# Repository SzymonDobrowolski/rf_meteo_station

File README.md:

# 🌤️ RF Meteo Station - Custom ESP32 Weather System

A complete, end-to-end open-source weather station project. This system combines custom hardware design, 3D-printed enclosures, and an advanced multithreaded firmware architecture to deliver a modern, touch-enabled weather dashboard.

---

## 1. ⚡ PCB Design (Custom Hardware)
The hardware architecture is divided into two separate custom-designed printed circuit boards:

* **Main Indoor Unit:** Houses the ESP32 microcontroller, power management, display connector (SPI), and the nRF24L01 radio receiver.
* **External Sensor Node:** A low-power, battery-operated board featuring environmental sensors and an nRF24L01 transmitter to send data wirelessly to the main unit.

| Main Board | External Sensor Board |
|:---:|:---:|
|  |  |

**📄 Full Schematics (PDF):**
* [Open Main Board Schematic PDF](images/int_scheme.pdf)
* [Open Sensor Board Schematic PDF](images/ext_scheme.pdf)

---

## 2. 🧊 Enclosure Design (3D Models)
To make the project a fully finished product, custom enclosures were modeled from scratch and 3D printed.

* **Main Display Case:** Designed to perfectly fit the touch screen, custom PCB, and provide easy access to power ports.
* **Outdoor Sensor Shield:** Features a Stevenson screen-inspired design to protect the external PCB from rain and direct sunlight while allowing accurate temperature and humidity readings.

| Display Enclosure | Sensor Enclosure |
|:---:|:---:|
|  |  |

---

## 3. 💻 Code Architecture & Features
The firmware is built on top of the **ESP-IDF** framework and utilizes **FreeRTOS** to handle multiple background tasks without blocking the UI. 

### Key Software Features:
* **Advanced GUI (LVGL):** A fluid, touch-optimized interface featuring a dashboard, 24h interactive charts, and a 7-day forecast. The UI logic is completely decoupled from the system core.
* **Multithreading:** Dedicated FreeRTOS tasks for display rendering, wireless data receiving (nRF24L01), and Wi-Fi management.
* **Live Weather API:** Fetches and parses real-time forecast data via the Open-Meteo API using `cJSON`.
* **Smart Power Management:** Features a Day/Night mode with a PWM soft-start mechanism to prevent sudden power spikes and brownout resets.
* **NVS Storage:** Safely retains Wi-Fi credentials, location preferences, and brightness settings between reboots.
* **SNTP Time Sync:** Automatically maintains atom-accurate system time in the background.
* **Display Support:** Codebase is optimized for **ST7789** controllers with easy migration to **ILI9341** via the `esp_lcd` framework.

---

## 4. 🚀 How to Build & Flash
The software is designed for the Espressif ESP-IDF framework (v5.0 or newer).

**Step 1: Clone the repository**
```bash
git clone [https://github.com/SzymonDobrowolski/rf_meteo_station.git](https://github.com/SzymonDobrowolski/rf_meteo_station.git)
cd rf_meteo_station/ESP32_int_station_code/internal_module_code_ST7789
```

**Step 2: Install Display Dependencies (ILI9341 Only)**
*Note: The default codebase is optimized for the ST7789 controller. If your specific build uses the ILI9341 display, you must add the official driver component before building:*
```bash
idf.py add-dependency "espressif/esp_lcd_ili9341"
```

**Step 3: Build and Flash**
Connect your ESP32 board and run the following commands:
```bash
idf.py set-target esp32
idf.py build
idf.py -p (YOUR_PORT) flash monitor
```

---

## 5. 🌟 Final Result
Here is the fully assembled, programmed, and working RF Meteo Station in action!

<p align="center">
  
  &nbsp;
  
</p>

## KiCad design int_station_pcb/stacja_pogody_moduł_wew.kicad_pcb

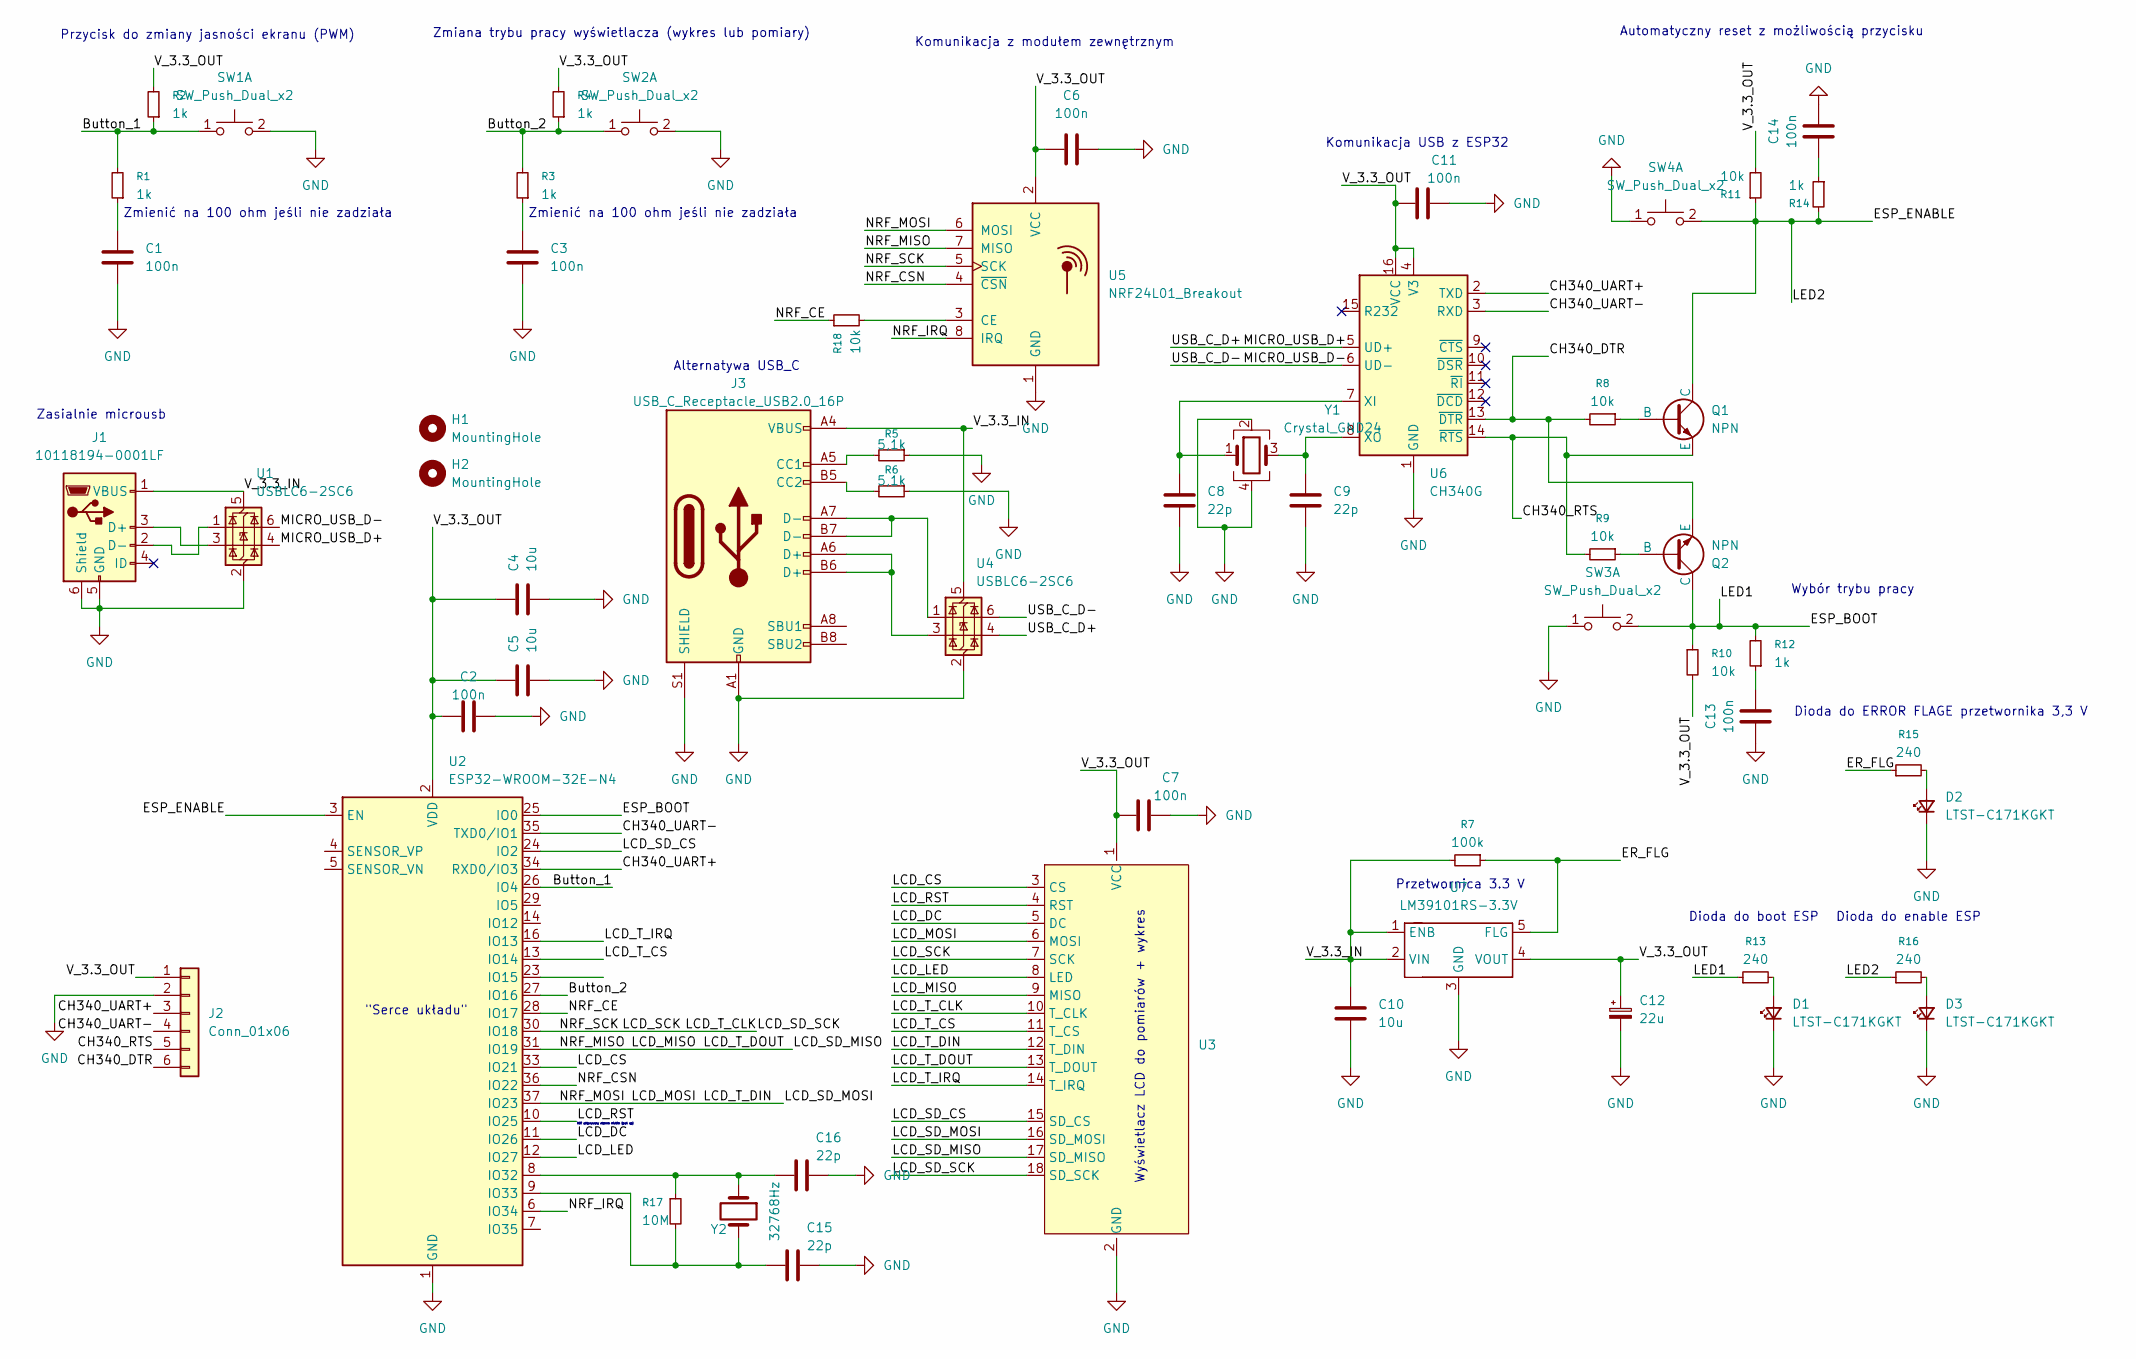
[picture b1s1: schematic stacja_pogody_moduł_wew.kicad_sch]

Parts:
C1, C2, C3, C6, C7, C11, C13, C14: 100n; C_0603_1608Metric_Pad1.08x0.95mm_HandSolder
C4, C5, C10: 10u; C_0805_2012Metric_Pad1.18x1.45mm_HandSolder
C8, C9: 22p; C_0805_2012Metric_Pad1.18x1.45mm_HandSolder
C12: 22u; CP_EIA-3528-21_Kemet-B_HandSolder
C15, C16: 22p; C_0603_1608Metric_Pad1.08x0.95mm_HandSolder
D1, D2, D3: LTST-C171KGKT; LED_0805_2012Metric
H1, H2: MountingHole; MountingHole_3.2mm_M3
J1: 10118194-0001LF; USB_Micro-B_Amphenol_10118194-0001LF_Horizontal
J2: Conn_01x06; PinSocket_1x06_P2.54mm_Vertical
J3: USB_C_Receptacle_USB2.0_16P; USB_C_Receptacle_TME
Q1, Q2: NPN; SOT-23_Handsoldering
R1, R2, R3, R4, R12, R14: 1k; R_0603_1608Metric
R5, R6: 5,1k; R_0603_1608Metric
R7: 100k; R_0603_1608Metric
R8, R9, R10, R11, R18: 10k; R_0603_1608Metric
R13, R15, R16: 240; R_0603_1608Metric
R17: 10M; R_0603_1608Metric
SW1, SW2, SW3, SW4: SW_Push_Dual_x2; SW_PUSH_6mm_H4.3mm
U1, U4: USBLC6-2SC6; SOT-23-6
U2: ESP32-WROOM-32E-N4; ESP32-WROOM-32E
U3: LCD_2_8
U5: NRF24L01_Breakout; nRF24L01_Breakout
U6: CH340G; SOIC-16_3.9x9.9mm_P1.27mm
U7: LM39101RS-3.3V; TO-252-5_TabPin3
Y1: Crystal_GND24; Crystal_SMD_3225-4Pin_3.2x2.5mm_HandSoldering
Y2: 32768Hz; Crystal_DS26_D2.0mm_L6.0mm_Horizontal

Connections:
/Button_1: R1.2, R2.1, SW1.1 (C), U2.26 (IO4)
/Button_2: R3.2, R4.1, SW2.1 (C), U2.27 (IO16)
/CH340_DTR: J2.6, Q2.3 (E), R8.2, U6.13 (~DTR)
/CH340_RTS: J2.5, Q1.3 (E), R9.2, U6.14 (~RTS)
/CH340_UART+: J2.3, U2.34 (RXD0/IO3), U6.2 (TXD)
/CH340_UART-: J2.4, U2.35 (TXD0/IO1), U6.3 (RXD)
/ER_FLG: R7.1, R15.1, U7.5 (FLG)
/ESP_BOOT: Q2.1 (C), R10.1, R12.2, R13.1, SW3.2 (D), U2.25 (IO0)
/ESP_ENABLE: Q1.1 (C), R11.1, R14.2, R16.1, SW4.2 (D), U2.3 (EN)
/LCD_CS: U2.33 (IO21), U3.3 (CS)
/LCD_DC: U2.11 (IO26), U3.5 (DC)
/LCD_LED: U2.12 (IO27), U3.8 (LED)
/LCD_MISO: U2.31 (IO19), U3.9 (MISO), U3.13 (T_DOUT), U3.17 (SD_MISO), U5.7 (MISO)
/LCD_MOSI: U2.37 (IO23), U3.6 (MOSI), U3.12 (T_DIN), U3.16 (SD_MOSI), U5.6 (MOSI)
/LCD_RST: U2.10 (IO25), U3.4 (RST)
/LCD_SCK: U2.30 (IO18), U3.7 (SCK), U3.10 (T_CLK), U3.18 (SD_SCK), U5.5 (SCK)
/LCD_SD_CS: U2.24 (IO2), U3.15 (SD_CS)
/LCD_T_CS: U2.13 (IO14), U3.11 (T_CS)
/LCD_T_IRQ: U2.16 (IO13), U3.14 (T_IRQ)
/MICRO_USB_D+: U1.4 (I/O2), U4.4 (I/O2), U6.5 (UD+)
/MICRO_USB_D-: U1.6 (I/O1), U4.6 (I/O1), U6.6 (UD-)
/NRF_CE: R18.1, U2.28 (IO17)
/NRF_CSN: U2.36 (IO22), U5.4 (~CSN)
/NRF_IRQ: U2.6 (IO34), U5.8 (IRQ)
/V_3.3_IN: C10.2, J1.1 (VBUS), J3.A4 (VBUS), J3.A9 (VBUS), J3.B4 (VBUS), J3.B9 (VBUS), R7.2, U1.5 (VBUS), U4.5 (VBUS), U7.1 (ENB), U7.2 (VIN)
/V_3.3_OUT: C2.2, C4.2, C5.2, C6.2, C7.2, C11.2, C12.1, J2.1, R2.2, R4.2, R10.2, R11.2, U2.2 (VDD), U3.1 (VCC), U5.2 (VCC), U6.4 (V3), U6.16 (VCC), U7.4 (VOUT)
GND: C1.1, C2.1, C3.1, C4.1, C5.1, C6.1, C7.1, C8.2, C9.2, C10.1, C11.1, C12.2, C13.2, C14.2, C15.1, C16.1, D1.1 (K), D2.1 (K), D3.1 (K), J1.5 (GND), J1.6 (Shield), J2.2, J3.A1 (GND), J3.A12 (GND), J3.B1 (GND), J3.B12 (GND), J3.S1 (SHIELD), R5.1, R6.1, SW1.2 (D), SW2.2 (D), SW3.1 (C), SW4.1 (C), U1.2 (GND), U2.1 (GND), U2.15 (GND), U2.38 (GND), U2.39 (GND), U3.2 (GND), U4.2 (GND), U5.1 (GND), U6.1 (GND), U7.3 (GND), Y1.2, Y1.4
unnamed: C1.2, R1.1
unnamed: C3.2, R3.1
unnamed: C13.1, R12.1
unnamed: C14.1, R14.1
unnamed: D1.2 (A), R13.2
unnamed: D2.2 (A), R15.2
unnamed: D3.2 (A), R16.2
unnamed: J1.3 (D+), U1.3 (I/O2)
unnamed: J1.2 (D-), U1.1 (I/O1)
unnamed: J3.A5 (CC1), R5.2
unnamed: J3.B5 (CC2), R6.2
unnamed: J3.A6 (D+), J3.B6 (D+), U4.3 (I/O2)
unnamed: J3.A7 (D-), J3.B7 (D-), U4.1 (I/O1)
unnamed: Q1.2 (B), R8.1
unnamed: Q2.2 (B), R9.1
unnamed: C16.2, R17.1, U2.8 (IO32), Y2.1
unnamed: C15.2, R17.2, U2.9 (IO33), Y2.2
unnamed: R18.2, U5.3 (CE)
unnamed: C8.1, U6.7 (XI), Y1.1
unnamed: C9.1, U6.8 (XO), Y1.3

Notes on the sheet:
Wyświetlacz LCD do pomiarów + wykres
Komunikacja z modułem zewnętrznym
Zmienić na 100 ohm jeśli nie zadziała
Zasialnie microusb
Wybór trybu pracy
Dioda do enable ESP
Automatyczny reset z możliwością przycisku
Dioda do boot ESP
RST aktywowany stanem niskim (pull up)
Alternatywa USB_C
Dioda do ERROR FLAGE przetwornika 3,3 V
Komunikacja USB z ESP32
Zmiana trybu pracy wyświetlacza (wykres lub pomiary)
Przycisk do zmiany jasności ekranu (PWM)
"Serce układu"
Przetwornica 3.3 V

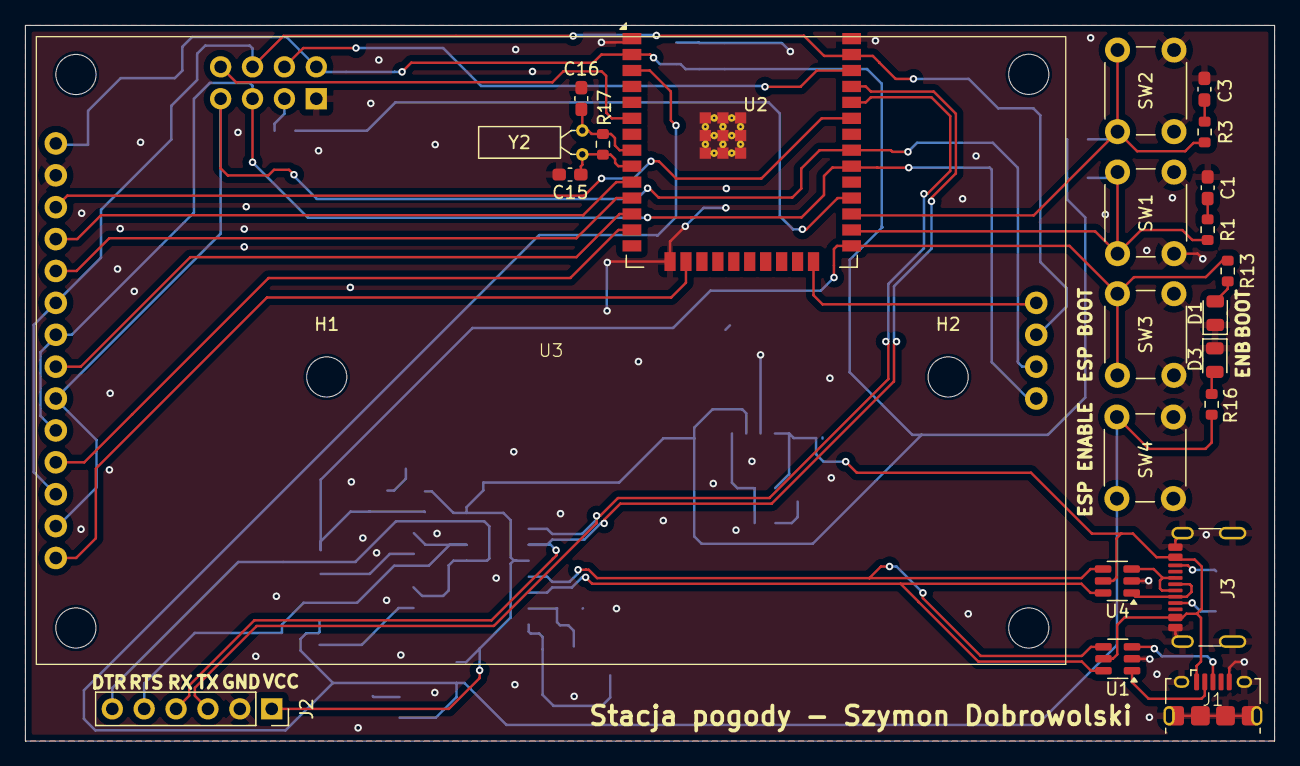
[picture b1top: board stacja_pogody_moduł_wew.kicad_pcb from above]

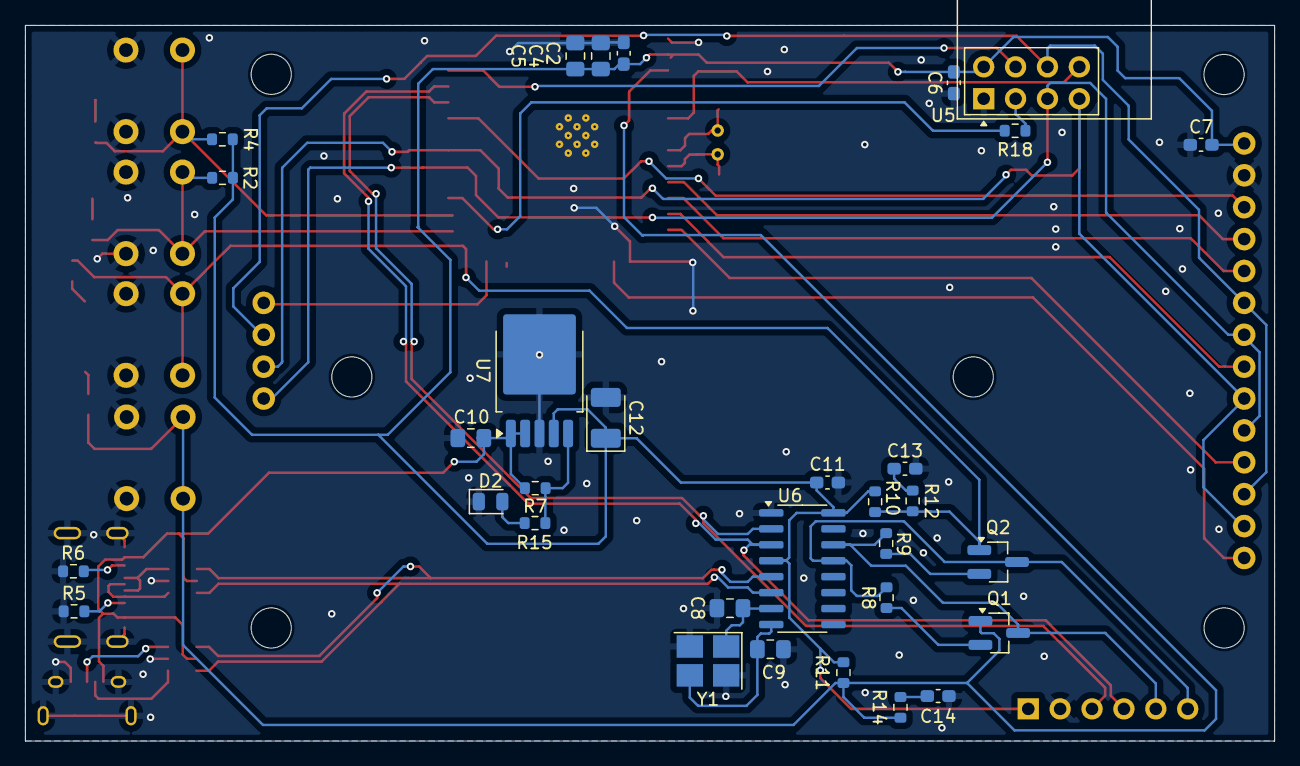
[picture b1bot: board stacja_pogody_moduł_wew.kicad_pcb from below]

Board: 2 copper layers, 99.5 x 57.0 mm, 57 parts (32 on the bottom side), 47 nets.

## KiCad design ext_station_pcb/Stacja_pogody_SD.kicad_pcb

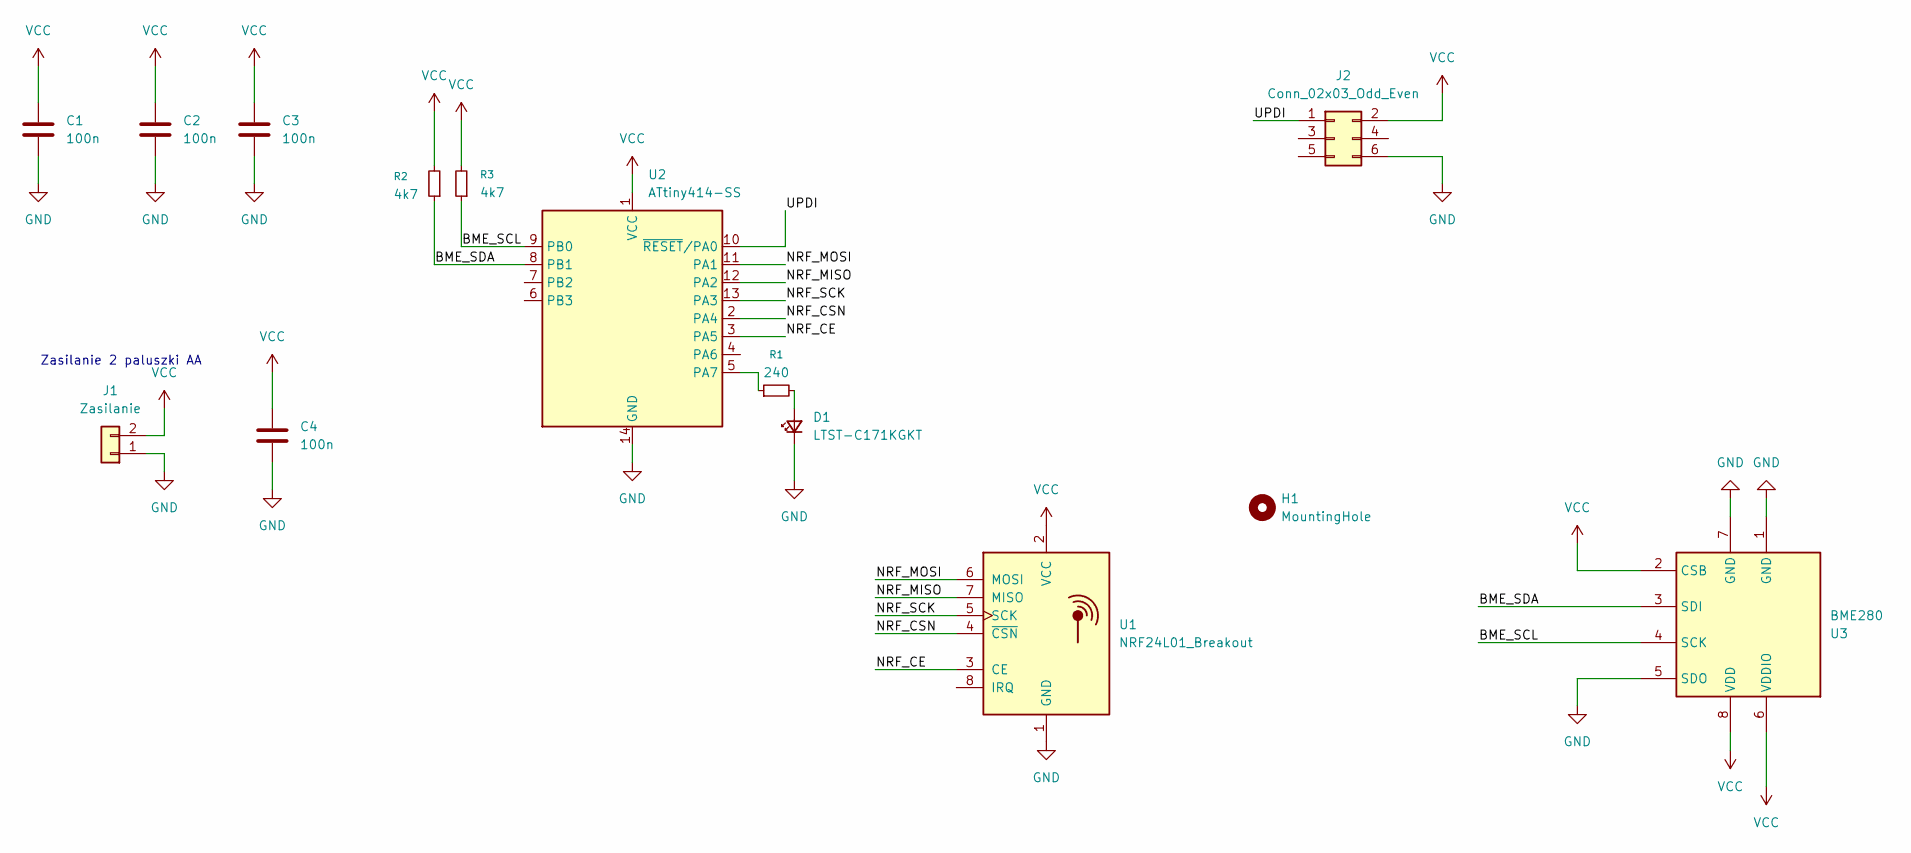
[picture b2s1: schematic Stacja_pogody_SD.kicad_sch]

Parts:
C1, C2, C3, C4: 100n; C_0603_1608Metric
D1: LTST-C171KGKT; LED_0805_2012Metric
H1: MountingHole; MountingHole_3.2mm_M3
J1: Zasilanie; PinHeader_1x02_P2.54mm_Vertical
J2: Conn_02x03_Odd_Even; PinHeader_2x03_P2.54mm_Vertical
R1: 240; R_0603_1608Metric
R2, R3: 4k7; R_0603_1608Metric
U1: NRF24L01_Breakout; nRF24L01_Breakout
U2: ATtiny414-SS; SOIC-14_3.9x8.7mm_P1.27mm
U3: BME280; Bosch_LGA-8_2.5x2.5mm_P0.65mm_ClockwisePinNumbering

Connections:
/BME_SCL: R3.1, U2.9 (PB0), U3.4 (SCK)
/BME_SDA: R2.1, U2.8 (PB1), U3.3 (SDI)
/NRF_CE: U1.3 (CE), U2.3 (PA5)
/NRF_CSN: U1.4 (~CSN), U2.2 (PA4)
/NRF_MISO: U1.7 (MISO), U2.12 (PA2)
/NRF_MOSI: U1.6 (MOSI), U2.11 (PA1)
/NRF_SCK: U1.5 (SCK), U2.13 (PA3)
/UPDI: J2.1, U2.10 (~RESET/PA0)
GND: C1.1, C2.1, C3.1, C4.1, D1.1 (K), J1.1, J2.6, U1.1 (GND), U2.14 (GND), U3.1 (GND), U3.5 (SDO), U3.7 (GND)
unnamed: D1.2 (A), R1.2
unnamed: R1.1, U2.5 (PA7)
VCC: C1.2, C2.2, C3.2, C4.2, J1.2, J2.2, R2.2, R3.2, U1.2 (VCC), U2.1 (VCC), U3.2 (CSB), U3.6 (VDDIO), U3.8 (VDD)

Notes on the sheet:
Zasilanie 2 paluszki AA

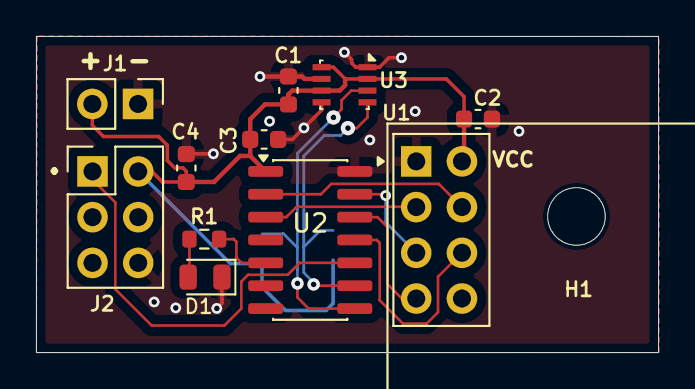
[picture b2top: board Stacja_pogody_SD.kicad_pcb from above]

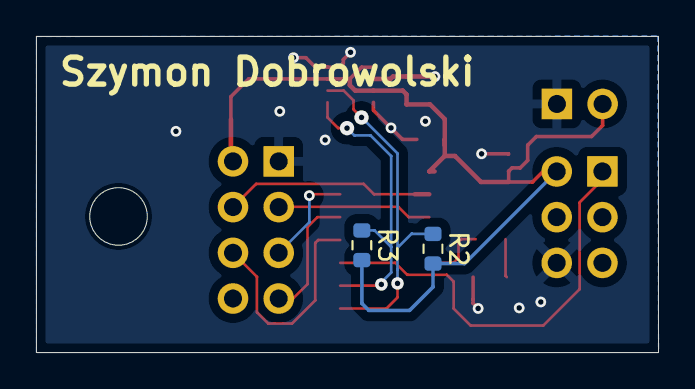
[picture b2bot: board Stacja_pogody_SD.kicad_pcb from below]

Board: 2 copper layers, 34.6 x 17.6 mm, 14 parts (2 on the bottom side), 12 nets.

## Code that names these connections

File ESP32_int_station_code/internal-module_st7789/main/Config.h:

#pragma once
#define BUTTON_1 GPIO_NUM_36
#define BUTTON_2 GPIO_NUM_39

#define LED1 GPIO_NUM_13
#define LED2 GPIO_NUM_21

// SPI Pins
#define SPI_MISO GPIO_NUM_19
#define SPI_MOSI GPIO_NUM_23
#define SPI_SCLK GPIO_NUM_18

// NRF Pins
#define NRF_CE_PIN GPIO_NUM_22
#define NRF_CSN_PIN GPIO_NUM_16
//NRF Settings
#define RX_ADDRESS_VAL {'A', 'T', '4', '1', '4'}
#define Channel 76
#define NRF_SPEED 0x07 //2Mbps, 0dBm

// --- STRUKTURA DANYCH (12 bajtów) ---
typedef struct __attribute__((packed)) {
    int32_t temp_hundredths;
    uint32_t pressure_pa;
    uint32_t hum_x1024;
} SensorData;

// LCD Pins
#define CS_PIN GPIO_NUM_4
#define DC_PIN GPIO_NUM_26
#define RESET_PIN GPIO_NUM_25
#define BL_PIN GPIO_NUM_27
//LCD Settings
#define LCD_TYPE 0x7789
#define LCD_WIDTH  320
#define LCD_HEIGHT 240
//Optional LCD
#define T_CS GPIO_NUM_14
#define SD_CS GPIO_NUM_17

#define NRF_IRQ GPIO_NUM_34
#define T_IRQ GPIO_NUM_35

// NTC
#define SSID "POCO X3 NFC"
#define PASSWORD "Rafik123"
#define SNTP_SERVER "pool.ntp.org"

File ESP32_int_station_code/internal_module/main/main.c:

#include <stdio.h>
#include <string.h>
#include <driver/gpio.h>
#include <driver/spi_master.h>
#include <freertos/FreeRTOS.h>
#include <freertos/task.h>
#include <esp_spiffs.h>
#include <esp_log.h>

#include "ili9340.h"
#include "fontx.h"

#include "NRF24L01.h"


#define PIN_LCD_CS     4
#define PIN_LCD_DC     26
#define PIN_LCD_RST    25
#define PIN_LCD_LED    27

#define PIN_MISO 19
#define PIN_MOSI 23
#define PIN_SCK  18

typedef struct __attribute__((packed)) {
    float temperature_C;
    float humidity_pct;
    float pressure_hPa;
} sensor_packet_t;

spi_device_handle_t nrf_spi;
spi_device_handle_t spi_lcd;

void spi_bus_init()
{
    spi_bus_config_t buscfg = {
        .mosi_io_num = PIN_MOSI,
        .miso_io_num = PIN_MISO,
        .sclk_io_num = PIN_SCK,
        .quadwp_io_num = -1,
        .quadhd_io_num = -1,
        .max_transfer_sz = 4096,
    };
    spi_bus_initialize(SPI3_HOST, &buscfg, SPI_DMA_CH_AUTO);
}

TFT_t tft;
FontxFile fx[2];

void init_spiffs()
{
    esp_vfs_spiffs_conf_t conf = {
        .base_path = "/spiflash",
        .partition_label = NULL,
        .max_files = 5,
        .format_if_mount_failed = true
    };
    esp_err_t ret = esp_vfs_spiffs_register(&conf);
    if (ret != ESP_OK) {
        ESP_LOGE("SPIFFS", "Błąd montowania SPIFFS");
    } else {
        ESP_LOGI("SPIFFS", "SPIFFS zamontowany pod /spiflash");
    }
}

void lcd_init(void)
{
    spi_device_interface_config_t devcfg = {
        .clock_speed_hz = 40*1000*1000,  // 40 MHz
        .mode = 0,
        .spics_io_num = PIN_LCD_CS,
        .queue_size = 7,
        .pre_cb = NULL,
    };
    spi_bus_add_device(SPI3_HOST, &devcfg, &tft._TFT_Handle);

    lcdInit(&tft, 0x9341, 240, 320, 0, 0);
    lcdBacklightOn(&tft);

    lcdSetFontDirection(&tft, DIRECTION0);
}


void app_main(void)
{
    init_spiffs();
    spi_bus_init();
    nrf_spi_init();
    nrf_set_rx_mode();
    lcd_init();

    
    InitFontx(fx, "/spiflash/ILGH16XB.FNT", "");
     if (!OpenFontx(fx)) {
        ESP_LOGE("FONT", "Nie udało się otworzyć fontu");
    } else {
        ESP_LOGI("FONT", "Font otwarty poprawnie");
    }

    sensor_packet_t pkt;

    uint8_t rxbuf[32];

    while (1)
    {
        if(nrf_data_ready())
        {
            int len = nrf_read_payload(rxbuf, 32);
            printf("Len: %d\n", len);

            memcpy(&pkt.temperature_C, &rxbuf[0], 4);
            memcpy(&pkt.humidity_pct, &rxbuf[4], 4);
            memcpy(&pkt.pressure_hPa, &rxbuf[8], 4);

            char buf[64];
            lcdFillScreen(&tft, BLACK);

            // Temperatura
            sprintf(buf, "Temp: %.2f C", pkt.temperature_C);
            printf(buf);
            lcdDrawString(&tft, fx, 10, 40, (uint8_t*)buf, WHITE);

            // Wilgotność
            sprintf(buf, "Wilg: %.2f %%", pkt.humidity_pct);
            printf(buf);
            lcdDrawString(&tft, fx, 10, 70, (uint8_t*)buf, GREEN);

            // Ciśnienie
            sprintf(buf, "Cisn: %.2f hPa", pkt.pressure_hPa);
            printf(buf);
            lcdDrawString(&tft, fx, 10, 100, (uint8_t*)buf, CYAN);
        }
        vTaskDelay(pdMS_TO_TICKS(1000));
    }
    
}

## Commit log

2025-11-18 Dokumentacja do stacji zewnętrznej
2025-11-18 Projekt płytki drukowanej dla modułu wewnętrznego
2025-11-18 Prokelt płytki drukowanej dla modułu zewnętrznego
2025-11-19 dodanie folderu
2025-11-19 usuniecie plikow datasheet bo przenioslem do folderu
2025-11-19 stworzenie folderow do projektow pcb i dodanie plikow
2025-11-19 dodanie folderow w ktorych beda kody do mikrokontrolerow
2025-11-19 datasheet esp32
2025-11-23 kod do esp
2025-11-25 Dodanie kodu do ATtiny
2025-11-25 poprawa plytki wew i zew
2025-11-25 poprawa plytek
2025-11-25 Przygotowanie srodowiska dla ATtiny414
2025-11-25 poprawa gerberow wew
2025-11-25 dodanie uart_init
2025-11-26 skonczona plytka dla plytki zew
2025-11-26 powiekszyc sciezki do 0.2mm w wew
2025-11-26 dokonczona plytka wew
2025-11-26 skonczona plytka wewnetrzna
2025-11-29 Dodana obsluga I2C oraz czujnika BME
2025-11-30 Poprawa czytelnosci kodu, obsluga BME dokonczona
2025-11-30 Dodana obsluga SPI i NRF, przy dobrych wiatrach moze juz zadzialac caly czujnik
2025-11-30 Poprawiona nazwa projektu internal -> external
2025-12-01 inicjalizacja SPI
2025-12-01 SPI dla NRF niby zrobione
2025-12-02 poprawa footprintu usb
2025-12-06 Naprawienie swiecenia diody sygnalizacyjnej
2025-12-06 Usuniecie pustego folderu internal_module
2025-12-06 Program na obslugujacy nrf, lcd
2025-12-07 wgranie pierwszego kodu do sprawdzenia transmiji 07.12
2025-12-11 próba debugowania modułów radiowych
2025-12-11 niby kolejna poprawka
2025-12-13 działająca komunikacja nrf, jeszcze trzeba kod napisać do odczytu danych z BME bo chat usunął xD
2025-12-13 Aktywacja BME na ATtiny
2025-12-13 Przeniesienie konwersji na esp
2025-12-13 Kod do ATtiny całkowicie gotowy. Do zrobienia obsługa wyświetlacza, gpio i uart jak bedzie ten wewnętrzny transiver
2025-12-13 usuniecie starego
2025-12-14 Działający wyświetlacz
2025-12-14 zmieniona orientacja ekranu, dodanie jakiegoś bajeru, podchody pod zrobienie zegara
2025-12-15 Poprawa szaty graficznej i wgranie loga politechniki
2025-12-15 Działa zegarek
2026-01-21 małe zmiany
2026-01-29 Dziala odbieranie danych z czujnka, dodano plik Config.h, wprowadzono tryb uspienia
2026-01-29 Dodano wykres, zmieniono napisy
2026-02-02 Zrobiona wersja testowa z podwojnym buforowaniem.
2026-02-02 Zmiana zakresu wilgotnosci
2026-02-04 Kompatybilny kod internal-module-podwojne_buforowanie dla st oraz ili, zmiana wyswietlacza w pliku Config.h
2026-02-08 ext case prototype
2026-02-08 ext_station case
2026-02-08 ext_case update
2026-02-08 case update
2026-02-09 edit for ST7789 TFT controller
2026-02-23 Recode graphic driver to LVGL
2026-02-24 deviding code for ST7789 and ILI graphic driver
2026-02-24 WiFi status icon + new weather data design
2026-02-24 ext station battery status + settings button + touch
2026-03-04 wifi search added with refresh button and power signal symbol
2026-03-05 settings screen ready + prep for graph and weather info screens
2026-03-09 weather inf + graphs + put logo. Full working. Long distance check + code optimization
2026-03-09 battery status in mV
2026-03-09 new logo
2026-03-14 added code for ili9341 graphic driver
2026-03-15 photos of project
2026-03-15 Add README for RF Meteo Station project
    Added a comprehensive README for the RF Meteo Station project, detailing PCB design, enclosure design, code architecture, build instructions, and final results.
2026-03-15 Fix closing paragraph tag in README.md
2026-03-15 Revise images and schematic references in README
    Updated images and schematic links in README.
2026-03-15 case photos
2026-03-15 Update images in README for case models
2026-03-17 code for ILI9341 ready
